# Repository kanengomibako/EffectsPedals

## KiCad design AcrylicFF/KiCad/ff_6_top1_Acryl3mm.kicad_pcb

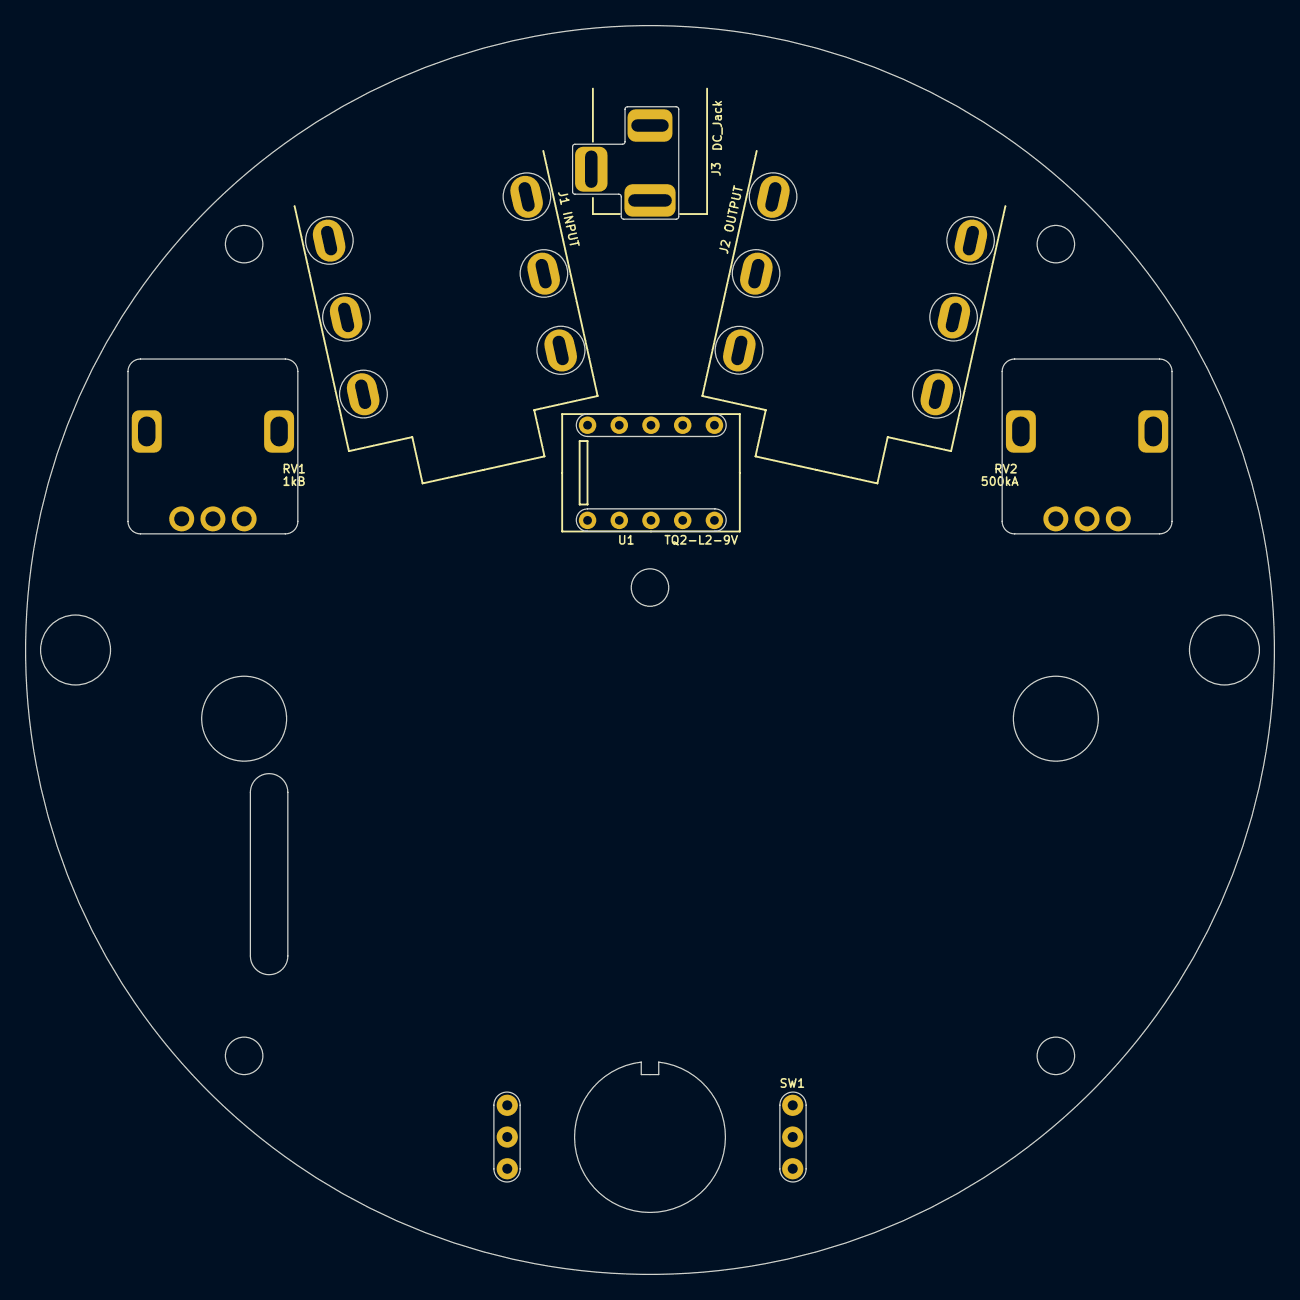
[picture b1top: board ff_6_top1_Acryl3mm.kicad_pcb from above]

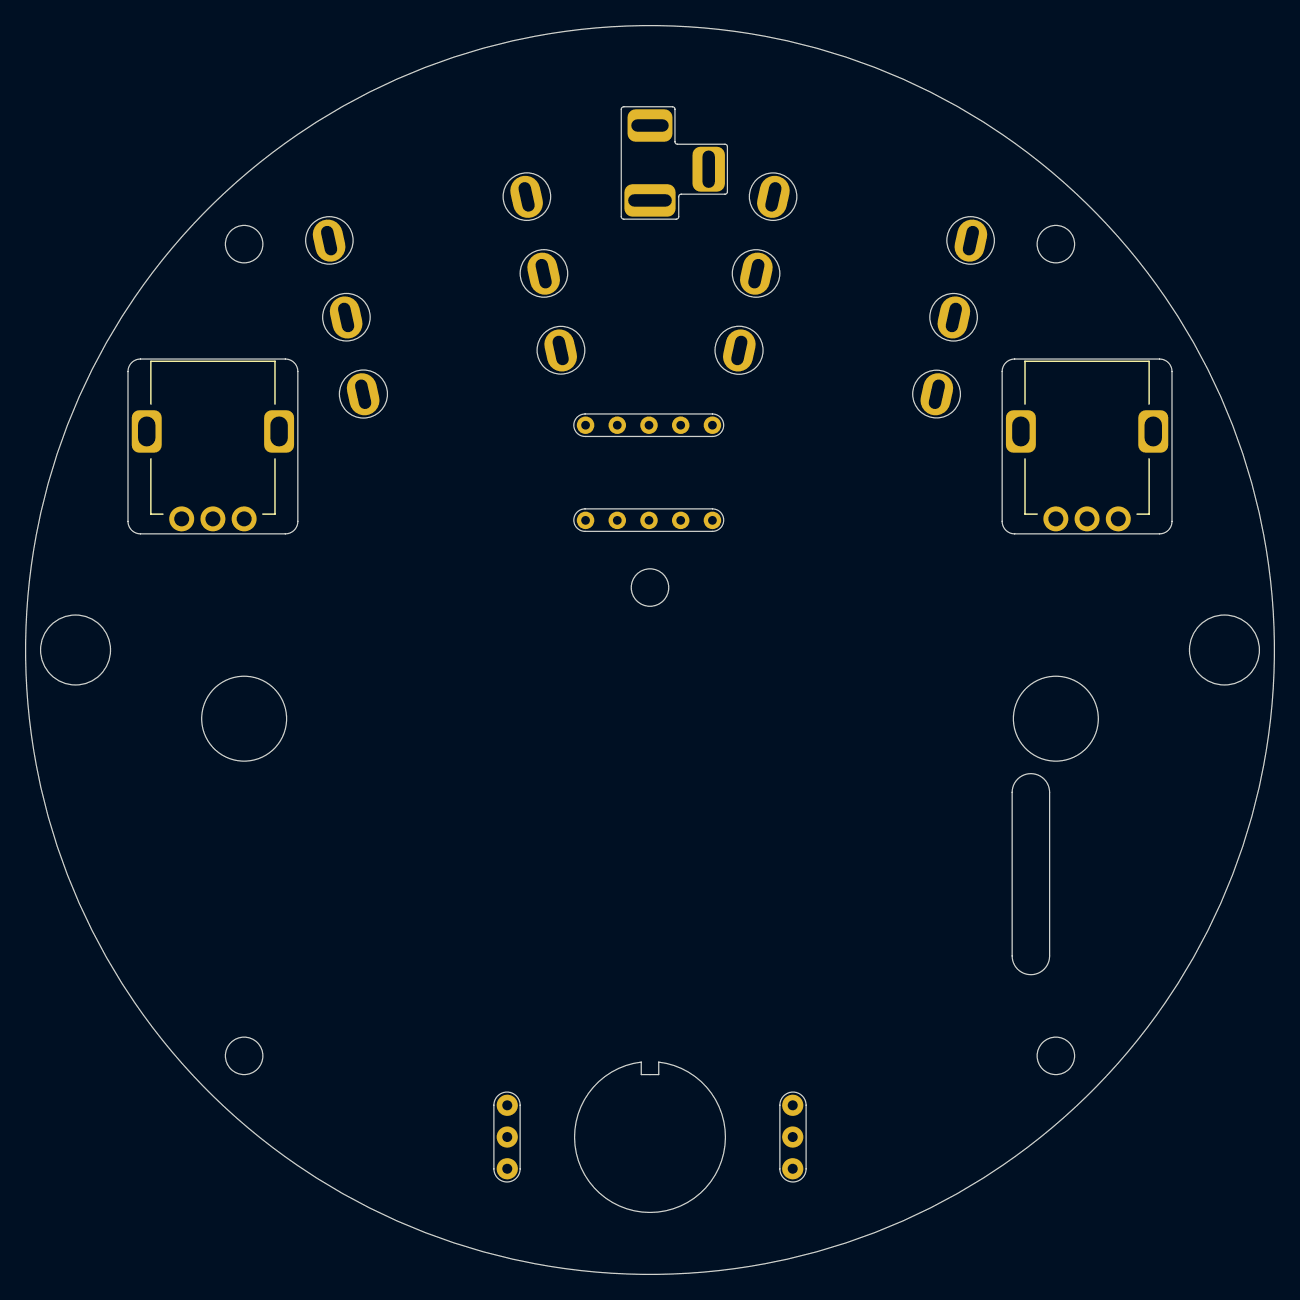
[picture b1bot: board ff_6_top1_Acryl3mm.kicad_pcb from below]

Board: 2 copper layers, 100.0 x 100.0 mm, 7 parts (2 on the bottom side), 5 nets, no tracks yet.

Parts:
J1: INPUT; my_Phone_Jack_Daier
J2: OUTPUT; my_Phone_Jack_Daier
J3: DC_Jack; my_DC_Jack
RV1: 1kB; my_Pot_PTV09A-4
RV2: 500kA; my_Pot_PTV09A-4
SW1: FS; my_SW_hanged
U1: TQ2-L2-9V; EA2-5TNAG

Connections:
+9V: J3.2, U1.1, U1.10
GND: J1.S, J1.SN, J1.TN, J2.S, J3.1, RV1.1, RV2.1, U1.2
unnamed: J1.T, U1.4, U1.9
unnamed: J2.T, U1.8
unnamed: RV2.2, U1.7

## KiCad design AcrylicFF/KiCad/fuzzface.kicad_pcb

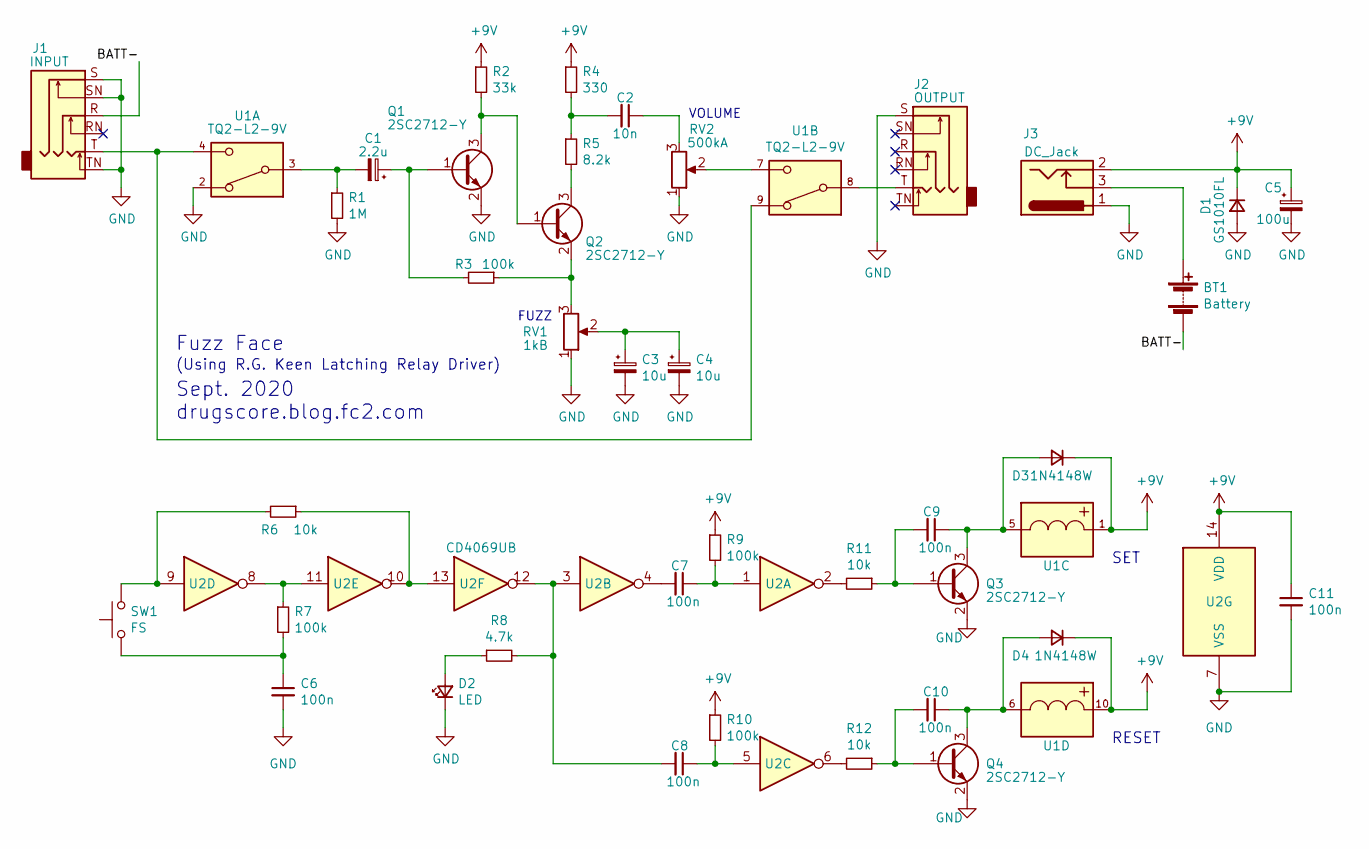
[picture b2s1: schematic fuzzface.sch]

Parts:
BT1: Battery; PinHeader_1x02_P2.54mm_Vertical
C1: 2.2u; my_C_2012(0805)_HandSoldering
C2: 10n; my_C_1608(0603)_HandSoldering
C3, C4: 10u; my_C_3216(1206)_HandSoldering
C5: 100u; my_C_Elec_6.3
C6, C7, C8, C9, C10, C11: 100n; my_C_1608(0603)_HandSoldering
D1: GS1010FL; my_D_GS1010FL
D2: LED; my_LED_3mm_Hole
D3, D4: 1N4148W; my_D_SOD-123
J1: INPUT; my_Phone_Jack_Daier
J2: OUTPUT; my_Phone_Jack_Daier
J3: DC_Jack; my_DC_Jack
Q1, Q2, Q3, Q4: 2SC2712-Y; my_SOT-23
R1: 1M; my_C_1608(0603)_HandSoldering
R2: 33k; my_C_1608(0603)_HandSoldering
R3, R7, R9, R10: 100k; my_C_1608(0603)_HandSoldering
R4: 330; my_C_2012(0805)_HandSoldering
R5: 8.2k; my_C_1608(0603)_HandSoldering
R6, R11, R12: 10k; my_C_1608(0603)_HandSoldering
R8: 4.7k; my_C_1608(0603)_HandSoldering
RV1: 1kB; my_Pot_PTV09A-4
RV2: 500kA; my_Pot_PTV09A-4
SW1: FS; my_SW_hanged
U1: TQ2-L2-9V; EA2-5TNAG
U2: CD4069UB; my_TSSOP-14

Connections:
+9V: C5.1, C11.1, D1.1 (K), D3.1 (K), D4.1 (K), J3.2, R2.1, R4.1, R9.1, R10.1, U1.1, U1.10, U2.14 (VDD); also elsewhere on the board
/BATT-: BT1.2 (-), J1.R
GND: C3.2, C4.2, C5.2, C6.2, C11.2, D1.2 (A), D2.1 (K), J1.S, J1.SN, J1.TN, J2.S, J3.1, Q1.2 (E), Q3.2 (E), Q4.2 (E), R1.2, RV1.1, RV2.1, U1.2, U2.7 (VSS); also elsewhere on the board
unnamed: BT1.1 (+), J3.3
unnamed: C1.1, Q1.1 (B), R3.2
unnamed: C1.2, R1.1, U1.3
unnamed: C2.1, RV2.3
unnamed: C2.2, R4.2, R5.1
unnamed: C3.1, C4.1, RV1.2
unnamed: C6.1, R7.2, SW1.1
unnamed: C7.1, R9.2, U2.1
unnamed: C7.2, U2.4
unnamed: C8.1, R10.2, U2.5
unnamed: C8.2, R8.2, U2.3, U2.12
unnamed: C9.1, D3.2 (A), Q3.3 (C), U1.5
unnamed: C9.2, Q3.1 (B), R11.1
unnamed: C10.1, D4.2 (A), Q4.3 (C), U1.6
unnamed: C10.2, Q4.1 (B), R12.1
unnamed: D2.2 (A), R8.1
unnamed: J1.T, U1.4, U1.9
unnamed: J2.T, U1.8
unnamed 26: Q1.3 (C), Q2.1 (B), R2.2; also elsewhere on the board
unnamed: Q2.2 (E), R3.1, RV1.3
unnamed: Q2.3 (C), R5.2
unnamed: R6.1, U2.10, U2.13
unnamed: R6.2, SW1.2, U2.9
unnamed: R7.1, U2.8, U2.11
unnamed: R11.2, U2.2
unnamed: R12.2, U2.6
unnamed: RV2.2, U1.7

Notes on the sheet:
Fuzz Face Sept. 2020 drugscore.blog.fc2.com
(Using R.G. Keen Latching Relay Driver)
SET
RESET
VOLUME
FUZZ

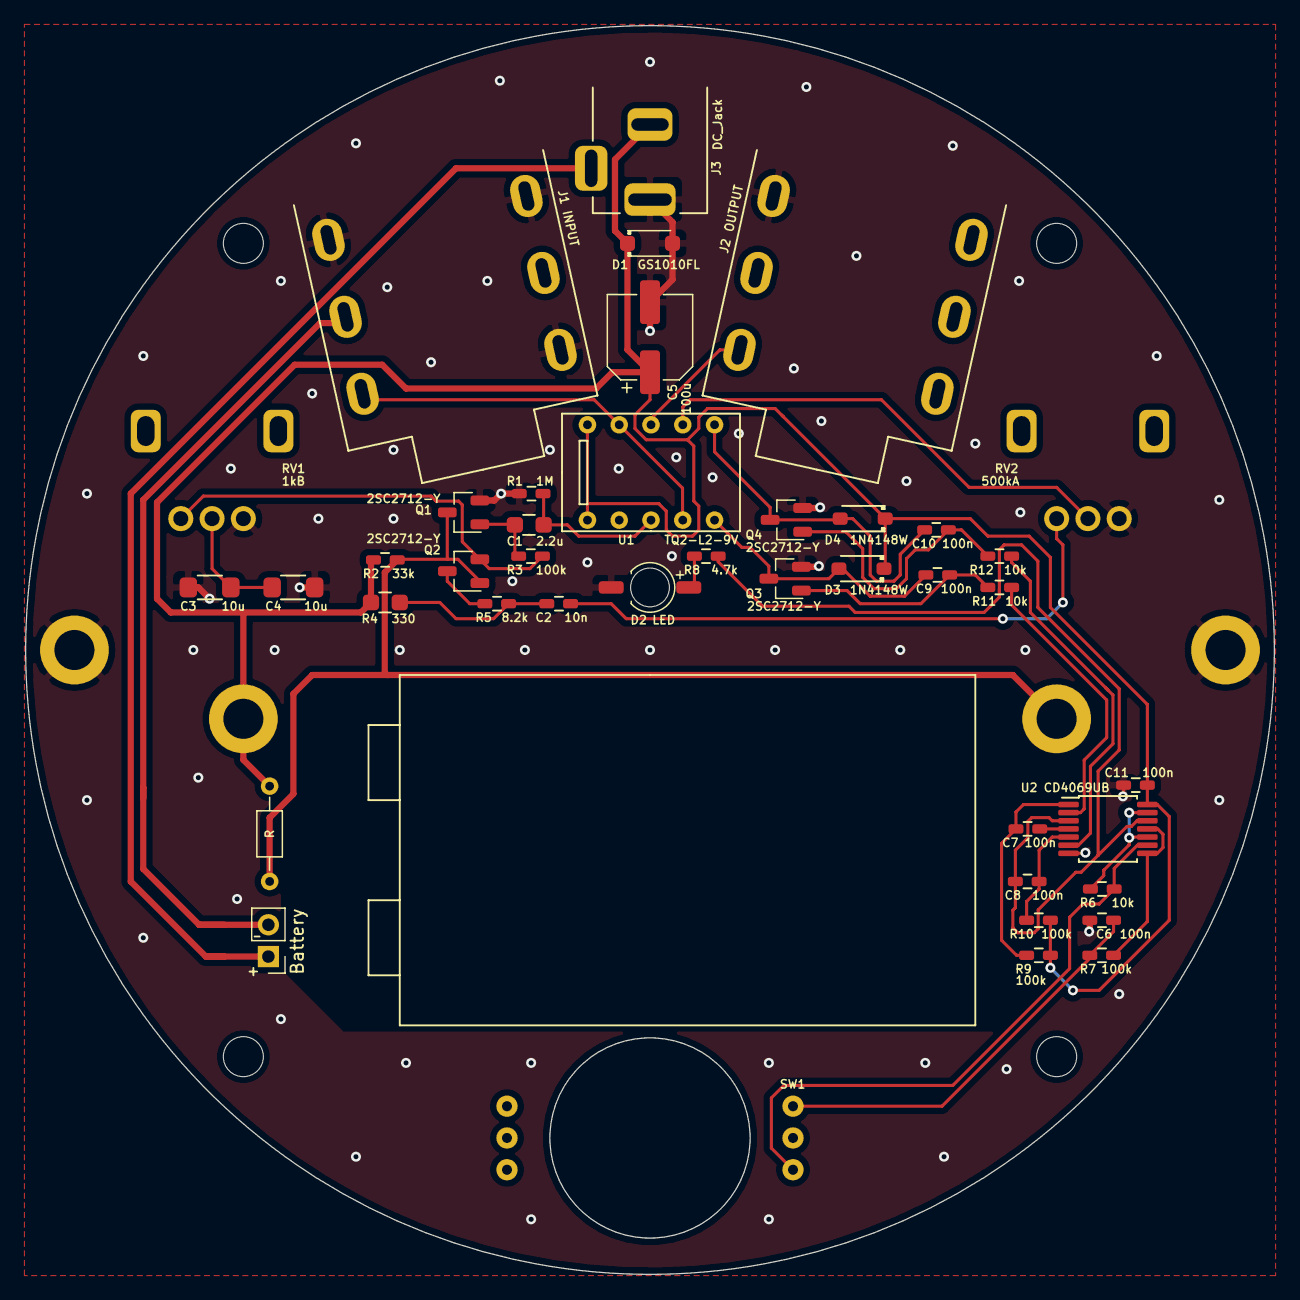
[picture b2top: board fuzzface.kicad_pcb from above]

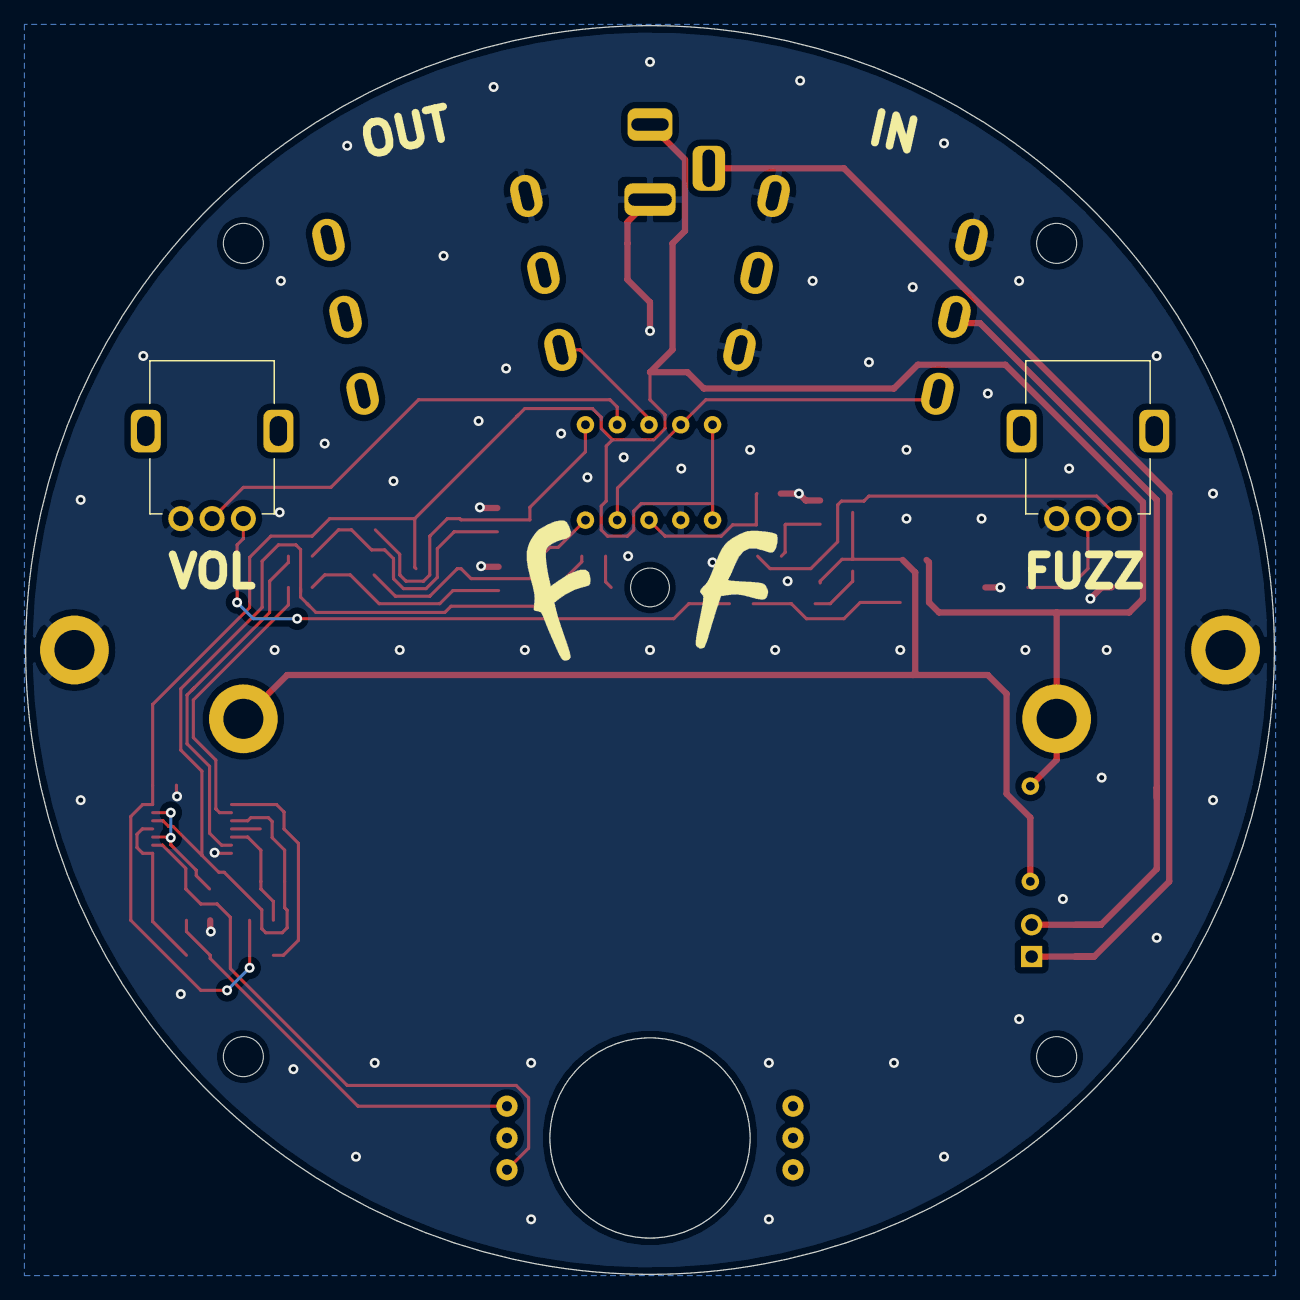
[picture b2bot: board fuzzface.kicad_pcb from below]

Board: 2 copper layers, 99.8 x 99.8 mm, 48 parts (2 on the bottom side), 30 nets.

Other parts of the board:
*: m; MountingHole_3.2mm_M3_ISO14580_Pad
*#2, *#6, *#7: m; MountingHole_3.2mm_M3_ISO14580_Pad
*#3, *#4, *#5, *#8: m; MountingHole_3.2mm_M3

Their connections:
+9V: *#2.1; also elsewhere on the board
GND: *#6.1, *#7.1; also elsewhere on the board
unnamed 26: *.1; also elsewhere on the board
